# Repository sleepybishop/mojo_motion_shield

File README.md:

# mojo_motion_shield
a motion shield for the mojo fpga

*  6 x Stepper Motor Outputs
*  6 x Encoder Inputs (A/B/I)
*  8 x PWM/Servo Outputs
*  8 x Analog Inputs
*  2 x SPI ports
*  2 x UART ports

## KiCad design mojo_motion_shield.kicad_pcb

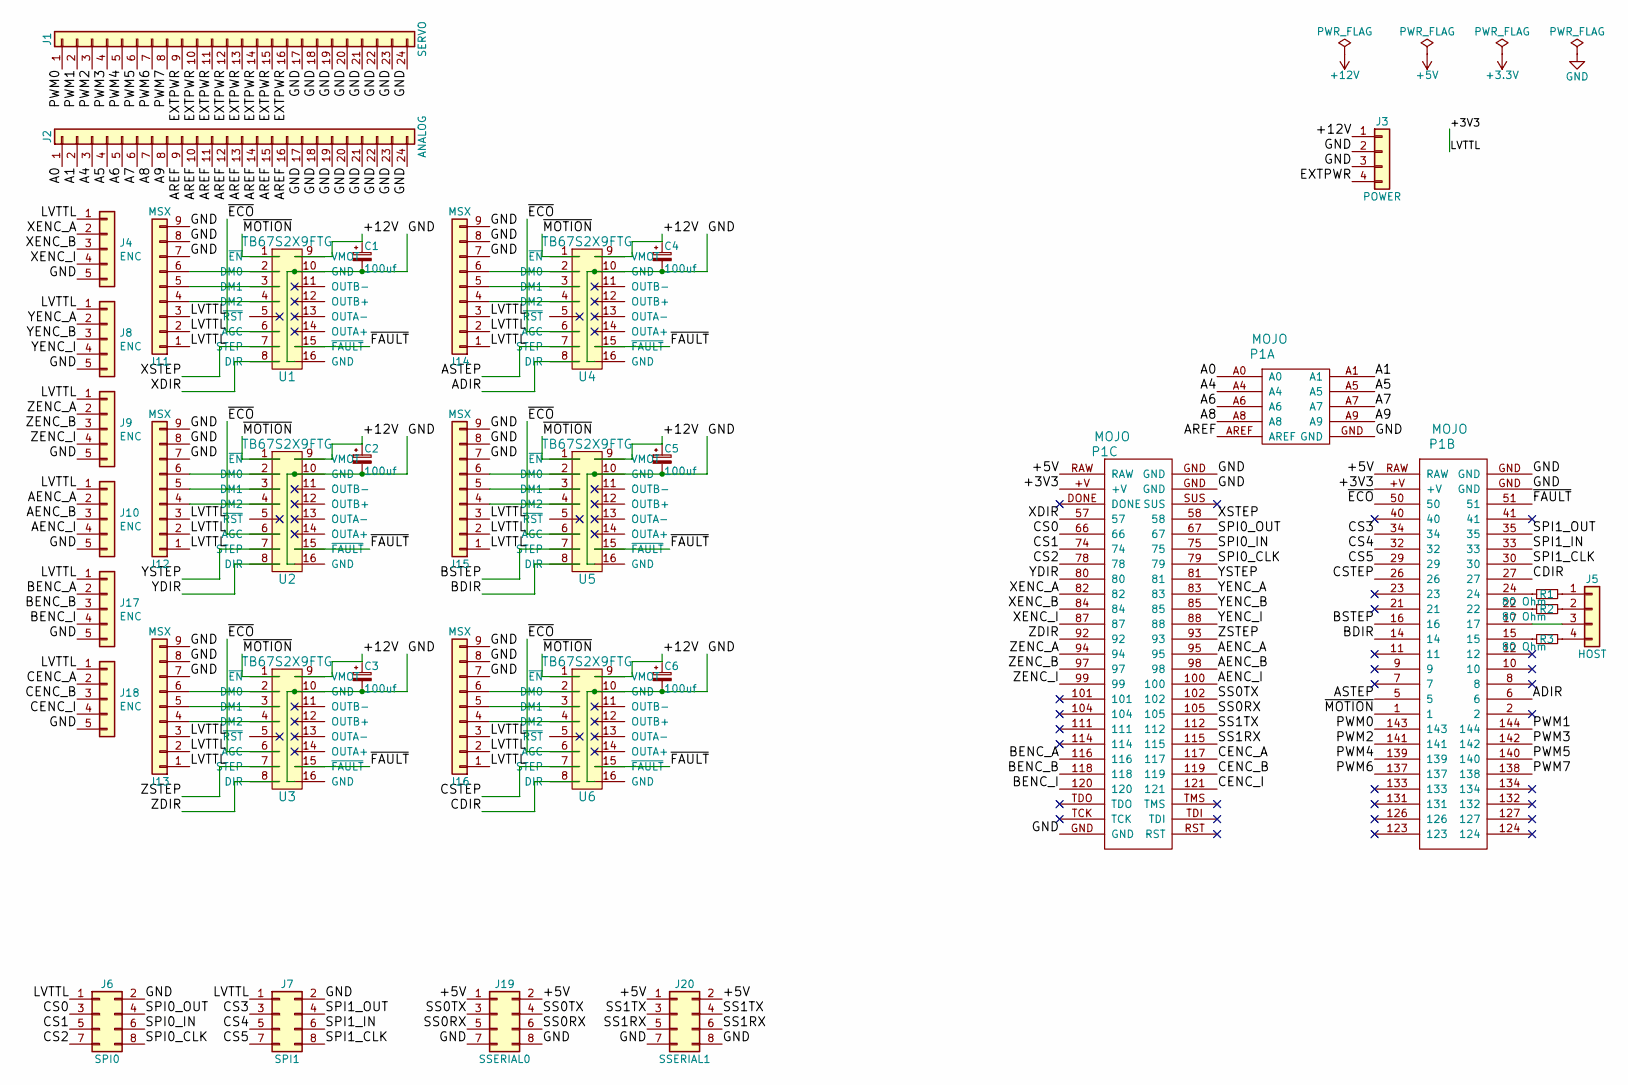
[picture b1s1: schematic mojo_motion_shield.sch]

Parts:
C1, C2, C3, C4, C5, C6: 100uf; CP_Radial_D5.0mm_P2.50mm
J1: SERVO; Pin_Header_Angled_3x08_Pitch2.54mm
J2: ANALOG; Pin_Header_Angled_3x08_Pitch2.54mm
J3: POWER; PhoenixContact_MC-G_04x5.08mm_Angled
J4, J8, J9, J10, J17, J18: ENC; PinHeader_1x05_P2.54mm_Vertical
J5: HOST; Pin_Header_Angled_1x04_Pitch2.54mm
J6: SPI0; Pin_Header_Straight_2x04_Pitch2.54mm
J7: SPI1; Pin_Header_Straight_2x04_Pitch2.54mm
J11, J12, J13, J14, J15, J16: MSX; Pin_Header_Straight_3x03_Pitch2.54mm
J19: SSERIAL0; PinHeader_2x04_P2.54mm_Vertical
J20: SSERIAL1; PinHeader_2x04_P2.54mm_Vertical
P1: MOJO; Mojo
R1, R2, R3: 80 Ohm; R_Axial_DIN0204_L3.6mm_D1.6mm_P2.54mm_Vertical
U1, U2, U3, U4, U5, U6: TB67S2X9FTG

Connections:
+3V3: J4.1, J6.1, J7.1, J8.1, J9.1, J10.1, J11.1, J11.2, J11.3, J12.1, J12.2, J12.3, J13.1, J13.2, J13.3, J14.1, J14.2, J14.3, J15.1, J15.2, J15.3, J16.1, J16.2, J16.3, J17.1, J18.1, P1.+V
+5V: J19.1, J19.2, J20.1, J20.2, P1.RAW
+12V: C1.1, C2.1, C3.1, C4.1, C5.1, C6.1, J3.1, U1.9 (VMOT), U2.9 (VMOT), U3.9 (VMOT), U4.9 (VMOT), U5.9 (VMOT), U6.9 (VMOT)
/A0: J2.1, P1.A0
/A1: J2.2, P1.A1
/A4: J2.3, P1.A4
/A5: J2.4, P1.A5
/A6: J2.5, P1.A6
/A7: J2.6, P1.A7
/A8: J2.7, P1.A8
/A9: J2.8, P1.A9
/ADIR: P1.6, U4.8 (DIR)
/AENC_A: J10.2, P1.95
/AENC_B: J10.3, P1.98
/AENC_I: J10.4, P1.100
/AREF: J2.9, J2.10, J2.11, J2.12, J2.13, J2.14, J2.15, J2.16, P1.AREF
/ASTEP: P1.5, U4.7 (STEP)
/BDIR: P1.14, U5.8 (DIR)
/BENC_A: J17.2, P1.116
/BENC_B: J17.3, P1.118
/BENC_I: J17.4, P1.120
/BSTEP: P1.16, U5.7 (STEP)
/CDIR: P1.27, U6.8 (DIR)
/CENC_A: J18.2, P1.117
/CENC_B: J18.3, P1.119
/CENC_I: J18.4, P1.121
/CS0: J6.3, P1.66
/CS1: J6.5, P1.74
/CS2: J6.7, P1.78
/CS3: J7.3, P1.34
/CS4: J7.5, P1.32
/CS5: J7.7, P1.29
/CSTEP: P1.26, U6.7 (STEP)
/EXTPWR: J1.9, J1.10, J1.11, J1.12, J1.13, J1.14, J1.15, J1.16, J3.4
/PWM0: J1.1, P1.143
/PWM1: J1.2, P1.144
/PWM2: J1.3, P1.141
/PWM3: J1.4, P1.142
/PWM4: J1.5, P1.139
/PWM5: J1.6, P1.140
/PWM6: J1.7, P1.137
/PWM7: J1.8, P1.138
/SPI0_CLK: J6.8, P1.79
/SPI0_IN: J6.6, P1.75
/SPI0_OUT: J6.4, P1.67
/SPI1_CLK: J7.8, P1.30
/SPI1_IN: J7.6, P1.33
/SPI1_OUT: J7.4, P1.35
/SS0RX: J19.5, J19.6, P1.105
/SS0TX: J19.3, J19.4, P1.102
/SS1RX: J20.5, J20.6, P1.115
/SS1TX: J20.3, J20.4, P1.112
/XDIR: P1.57, U1.8 (DIR)
/XENC_A: J4.2, P1.82
/XENC_B: J4.3, P1.84
/XENC_I: J4.4, P1.87
/XSTEP: P1.58, U1.7 (STEP)
/YDIR: P1.80, U2.8 (DIR)
/YENC_A: J8.2, P1.83
/YENC_B: J8.3, P1.85
/YENC_I: J8.4, P1.88
/YSTEP: P1.81, U2.7 (STEP)
/ZDIR: P1.92, U3.8 (DIR)
/ZENC_A: J9.2, P1.94
/ZENC_B: J9.3, P1.97
/ZENC_I: J9.4, P1.99
/ZSTEP: P1.93, U3.7 (STEP)
/~ECO: P1.50, U1.6 (AGC), U2.6 (AGC), U3.6 (AGC), U4.6 (AGC), U5.6 (AGC), U6.6 (AGC)
/~FAULT: P1.51, U1.15 (~FAULT), U2.15 (~FAULT), U3.15 (~FAULT), U4.15 (~FAULT), U5.15 (~FAULT), U6.15 (~FAULT)
/~MOTION: P1.1, U1.1 (~EN), U2.1 (~EN), U3.1 (~EN), U4.1 (~EN), U5.1 (~EN), U6.1 (~EN)
GND: C1.2, C2.2, C3.2, C4.2, C5.2, C6.2, J1.17, J1.18, J1.19, J1.20, J1.21, J1.22, J1.23, J1.24, J2.17, J2.18, J2.19, J2.20, J2.21, J2.22, J2.23, J2.24, J3.2, J3.3, J4.5, J6.2, J7.2, J8.5, J9.5, J10.5, J11.7, J11.8, J11.9, J12.7, J12.8, J12.9, J13.7, J13.8, J13.9, J14.7, J14.8, J14.9, J15.7, J15.8, J15.9, J16.7, J16.8, J16.9, J17.5, J18.5, J19.7, J19.8, J20.7, J20.8, P1.GND, U1.10 (GND), U1.16 (GND), U2.10 (GND), U2.16 (GND), U3.10 (GND), U3.16 (GND), U4.10 (GND), U4.16 (GND), U5.10 (GND), U5.16 (GND), U6.10 (GND), U6.16 (GND)
unnamed: J5.1, R1.2
unnamed: J5.2, R2.2
unnamed: J5.3, P1.17
unnamed: J5.4, R3.2
unnamed: J11.4, U1.4 (DM2)
unnamed: J11.5, U1.3 (DM1)
unnamed: J11.6, U1.2 (DM0)
unnamed: J12.4, U2.4 (DM2)
unnamed: J12.5, U2.3 (DM1)
unnamed: J12.6, U2.2 (DM0)
unnamed: J13.4, U3.4 (DM2)
unnamed: J13.5, U3.3 (DM1)
unnamed: J13.6, U3.2 (DM0)
unnamed: J14.4, U4.4 (DM2)
unnamed: J14.5, U4.3 (DM1)
unnamed: J14.6, U4.2 (DM0)
unnamed: J15.4, U5.4 (DM2)
unnamed: J15.5, U5.3 (DM1)
unnamed: J15.6, U5.2 (DM0)
unnamed: J16.4, U6.4 (DM2)
unnamed: J16.5, U6.3 (DM1)
unnamed: J16.6, U6.2 (DM0)
unnamed: P1.15, R3.1
unnamed: P1.22, R2.1
unnamed: P1.24, R1.1

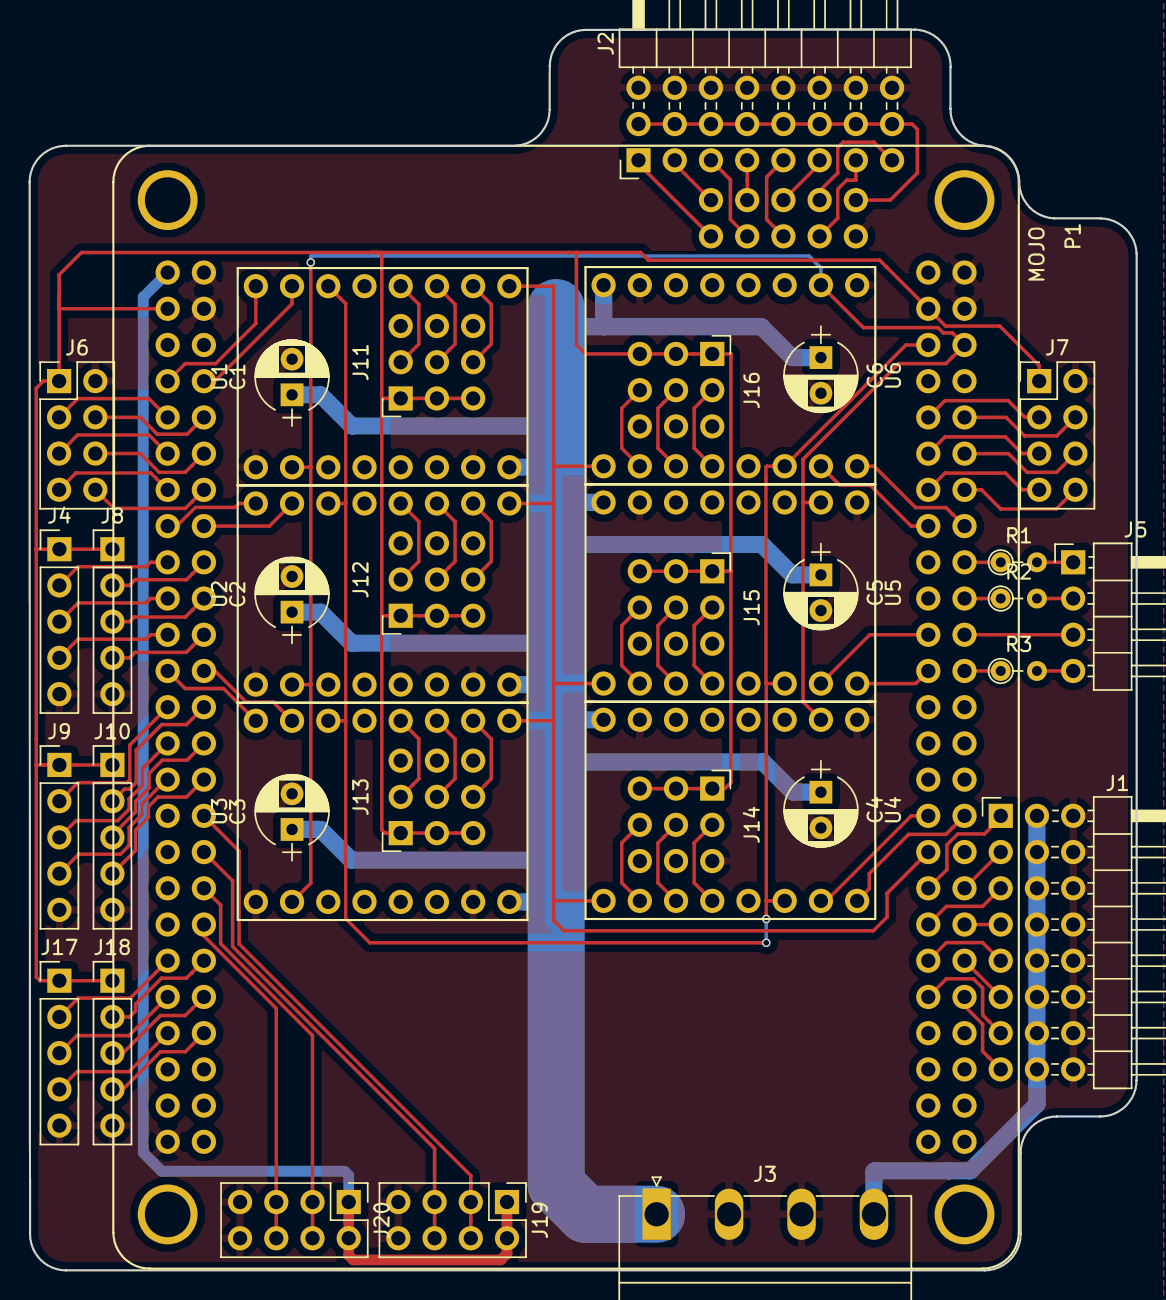
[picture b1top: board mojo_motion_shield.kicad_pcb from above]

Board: 2 copper layers, 77.6 x 87.0 mm, 36 parts (0 on the bottom side), 96 nets.

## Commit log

2017-12-29 flesh out schematic
2017-12-31 add custom footprint for a4988 carrier and 3x3, 3x8 pin headers
2017-12-31 flesh out pcb layout
2018-01-02 implement most of the routes
2019-05-13 update 6xTB67S249FTG shield
2019-05-14 route fault pins from drivers to fpga
2019-05-14 increase common motor power track width
2019-05-15 refactor port positions
